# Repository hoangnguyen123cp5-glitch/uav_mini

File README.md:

# UAV Mini — nền tảng drone học thuật chi phí thấp

**Mục tiêu:** phát triển kit học điều khiển từ Flix, có log, bài thực hành và hướng mở rộng ToF/optical flow. Crazyflie là mốc tham chiếu tính năng; chưa tuyên bố tương đương hoặc tương thích.

**Trạng thái 03/11/2026:** chưa mua phần cứng. Đã có **project KiCad DRAFT-0** với schematic và PCB bố trí thử (33 linh kiện, chưa đi dây), cùng firmware **chạy bàn, khóa đầu ra motor**, công cụ phân tích log và ngân sách mục tiêu. Chưa có thử nghiệm bay hoặc PCB hoàn chỉnh để gia công.

| Bắt đầu ở đây | Nội dung |
|---|---|
| [Mở project KiCad trên máy](hardware/kicad/UAV_Mini_RevA_Draft/README.md) | File schematic/PCB, preview, kết quả kiểm tra và hướng dẫn Windows |
| [Lộ trình kit học thuật](docs/ACADEMIC_PRODUCT_ROADMAP.md) | Core Lab → Research → nhiều drone, ngân sách và ticket |
| [Firmware chạy bàn](firmware/README.md) | Cách tải đúng upstream, build, cấu hình và giới hạn |
| [Kết quả kiểm tra](docs/VALIDATION.md) | Kiểm tra phần mềm đã chạy và phần chưa xác minh |
| [Nguồn và PCB Rev A](docs/REV_A_POWER_AND_PCB.md) | Nguồn, USB, linh kiện và kế hoạch KiCad |
| [Nguồn gốc và thương mại hóa](docs/COMMERCIALIZATION_NOTES.md) | Tình trạng giấy phép, phân phối và thương hiệu |

Chạy ngay trên máy tính tại thư mục repo (cần Python 3):

```bash
python3 tools/budget.py
python3 tools/analyze_log.py examples/synthetic_log.csv
```

Ví dụ CSV là dữ liệu tổng hợp, không phải kết quả bay. Phần dưới giữ lại bài học KiCad và cấu hình tham khảo trước khi chốt phần cứng.

## Học vẽ mạch điều khiển bằng KiCad

**ESP32-S3 SuperMini + 4 motor chổi than + IMU + ToF + optical flow**  
Cập nhật: 03/11/2026 • Project hiện tại: `Flix_power`

UAV Mini là dự án học thiết kế mạch cho drone nhỏ, tham khảo dự án mã nguồn mở [Flix](https://github.com/okalachev/flix). Mục tiêu là làm một PCB mang bốn kênh điều khiển động cơ và các cổng cảm biến, với bo ESP32-S3 SuperMini cắm lên trên.

**Tài liệu dành cho người mới chưa biết bắt đầu vẽ schematic từ đâu.** Bạn sẽ lần lượt vẽ đầu pin, một kênh motor, nhân thành bốn kênh, nối bo S3 và các cổng cảm biến, rồi kiểm tra kết nối bằng ERC.

Schematic là sơ đồ các linh kiện nối điện với nhau. PCB là bản bố trí linh kiện và đường đồng để gia công. Tài liệu này hướng dẫn phần schematic; chưa phải hướng dẫn hoàn chỉnh từ đầu đến một drone bay được.

> Dự án đang phát triển. Các giá trị có chữ TBD và phần nguồn S3 chưa được chốt. Bạn có thể dùng tài liệu để học vẽ, nhưng chưa dùng bản hiện tại để đặt PCB hoặc lắp cấp điện. [Project KiCad DRAFT-0](hardware/kicad/UAV_Mini_RevA_Draft/README.md) đã được kiểm tra đọc/xuất và đối chiếu net, còn 67 mục chưa nối dây, chưa ERC hoặc kiểm chứng phần cứng. Bài thực hành bên dưới giữ lại quy trình cũ; bản CAD mới dùng MOSFET **G1/S2/D3**, khác thứ tự GDS trong bài cũ, và thêm cầu hàn ADC mặc định mở.

Các ảnh chụp KiCad ở bài thực hành A–E là ảnh thật ghi lại từng bước vẽ của dự án. Chú thích ngay dưới ảnh chỉ rõ phần nào còn là bước trung gian hoặc thuộc phương án cũ. Bốn hình sơ đồ chức năng ở các mục tham khảo được vẽ riêng để giải thích kết nối.

## Bắt đầu từ đâu?

1. Cài KiCad, tạo **New Project** tên `Flix_power` trong một thư mục riêng.
2. Mở file `.kicad_sch` bằng Schematic Editor.
3. Đọc phần “Các khái niệm cần biết” bên dưới.
4. Làm lần lượt bài thực hành A–F; dùng bảng chân và hình ở các mục sau để đối chiếu.
5. Lưu file sau mỗi khối. Chạy ERC để tìm lỗi kết nối trước khi chuyển sang bố trí PCB.

### Các khái niệm cần biết

| Tên | Hiểu đơn giản |
|---|---|
| Symbol | Ký hiệu linh kiện trên schematic |
| Reference | Mã nhận diện riêng: J là đầu nối, R là điện trở, C là tụ, Q là transistor, D là diode |
| Value | Giá trị hoặc mã linh kiện, ví dụ 10k, 100nF |
| Wire | Dây thể hiện kết nối điện |
| Net label | Tên mạng điện; các dây có cùng local label trên cùng sheet nối điện với nhau dù không kéo dây dài |
| GND | Điểm tham chiếu chung của mạch |
| Footprint | Hình chân hàn và kích thước linh kiện trên PCB; chọn sau khi chốt linh kiện thật |
| ERC | Công cụ tìm một số lỗi kết nối trên schematic |
| TBD | Chưa chọn xong; đây không phải mã linh kiện để mua |

**Label phải có điểm neo chạm dây.** Chữ đặt gần dây chưa chắc đã nối điện. Số chân của connector cũng không phải số GPIO trên ESP32.

## Thao tác KiCad từng lệnh — đọc trước khi vẽ

Hướng dẫn dùng Schematic Editor trên Windows, với phím tắt mặc định. Khi bấm phím, đưa con trỏ vào vùng vẽ; nếu đang nhập chữ trong hộp thoại, phím sẽ nhập chữ thay vì chạy lệnh. Nếu đã đổi phím tắt, kiểm tra trong **Preferences → Preferences → Hotkeys**.

### 1. Tạo project và mở trang vẽ

1. Mở KiCad Project Manager.
2. Chọn **File → New Project**, chọn thư mục và nhập tên Flix_power.
3. Giữ tùy chọn tạo thư mục riêng cho project nếu hộp thoại có tùy chọn này, rồi lưu.
4. Trong danh sách file của project, mở **Flix_power.kicad_sch**. Đây là trang vẽ sơ đồ nguyên lý.
5. Nếu lần đầu KiCad hỏi thiết lập thư viện symbol, chọn thư viện mặc định được cài cùng KiCad.
6. Dùng lưới **50 mil** để đặt chân và dây. Cuộn bánh xe chuột để phóng to khu vực đang vẽ.

### 2. A — thêm linh kiện

Ví dụ thêm đầu pin J1:

1. Đưa chuột tới khoảng trống, nhấn **A**.
2. Trong cửa sổ Choose Symbol, gõ **Conn_01x02_Pin** vào ô tìm kiếm.
3. Chọn đúng kết quả, nhìn hình xem có hai chân đánh số 1 và 2, rồi bấm **OK**.
4. Symbol đi theo con trỏ. Di chuyển tới nơi muốn đặt, bấm chuột trái một lần.
5. Nhấn **Esc** để thoát chế độ đặt; nếu còn công cụ hoạt động, nhấn Esc thêm lần nữa.

Dùng cùng thao tác này cho từng linh kiện:

| Cần vẽ | Từ khóa tìm bằng A | Reference theo bài | Value nhập bằng E |
|---|---|---|---|
| Đầu pin | Conn_01x02_Pin | J1 | BATTERY_1S |
| Đầu motor | Conn_01x02_Pin | J2–J5 | Motor_0 đến Motor_3 |
| Tụ phân cực | Device:C_Polarized | C1 | BULK_TBD |
| Tụ không phân cực | Device:C | C2, C3 | 100nF |
| Điện trở | Device:R | R1–R10 | Theo bảng từng khối |
| MOSFET N | Q_NMOS_GDS | Q1–Q4 | NMOS_TBD |
| Diode Schottky | Device:D_Schottky | D1–D4 | SCHOTTKY_TBD |
| Socket S3 | Conn_01x09_Socket | J7, J8 | S3_LEFT, S3_RIGHT |
| Đầu ToF | Conn_01x04_Pin | J6 | TOF_I2C |
| Đầu IMU/flow | Conn_01x06_Pin | J9, J10 | IMU_SPI, FLOW_SPI |

Nếu không tìm thấy, bỏ phần tên thư viện trước dấu hai chấm và tìm lại. Không chọn đại linh kiện có chân khác. Pin/Socket trong tên symbol biểu diễn loại đầu nối; footprint thật và kích thước hàng chân vẫn cần chọn riêng.

### 3. E — sửa tên và giá trị

1. Nhấn Esc để thoát công cụ trước đó.
2. Rê chuột lên **thân symbol** J1, nhấn **E**. Nếu xuất hiện danh sách nhiều đối tượng, chọn symbol cần sửa.
3. Trong Symbol Properties, tìm hàng **Reference**, nhập J1.
4. Tìm hàng **Value**, nhập BATTERY_1S; bấm **OK**.
5. Kiểm tra trên trang vẽ có cả J1 và BATTERY_1S.

Với điện trở, nhập Value là 100R hoặc 10k theo bài. Reference phải duy nhất: R1 và R2 là hai linh kiện khác nhau. Chưa chốt linh kiện thật thì để trống Footprint; không chọn footprint tùy ý chỉ để đi tiếp.

### 4. R — xoay; M — di chuyển

- **Xoay:** rê chuột lên thân điện trở → nhấn **R** một lần để xoay 90°; nhấn thêm nếu cần. Khi symbol đang đi theo chuột lúc đặt, cũng dùng R rồi bấm trái để đặt.
- **Di chuyển:** rê chuột lên symbol → nhấn **M** → đưa đến vị trí mới → bấm trái.
- Sau khi di chuyển một linh kiện đã nối dây, kiểm tra lại các đầu dây. Có thể dùng **G** để kéo linh kiện cùng dây, nhưng vẫn cần xem lại kết nối.
- Nhấn **Esc** để hủy thao tác chưa đặt. Nhấn **Ctrl+Z** để hoàn tác thay đổi vừa thực hiện.

### 5. W — nối dây điện

Ví dụ nối chân 1 của J1 đến cực dương C1:

1. Đặt C1 ở bên phải J1, cực + hướng lên trên.
2. Rê chuột đúng **đầu ngoài chân 1** của J1, không đặt lên số 1 hay chữ J1.
3. Nhấn **W**; di chuyển chuột để kéo dây.
4. Bấm trái tại vị trí muốn tạo góc rẽ, rồi tiếp tục tới đầu chân + của C1.
5. Bấm trái đúng đầu chân C1 để hoàn thành kết nối. Nhấn Esc để thoát công cụ.
6. Nếu muốn kết thúc một đoạn dây ở khoảng trống để đặt label, **nhấp đúp** tại điểm cuối rồi Esc.

Dây là đối tượng Wire, không dùng đường đồ họa để thay dây điện. Đầu dây phải bắt đúng chân trên lưới.

**Tạo nhánh:** rê chuột lên dây có sẵn → W → kéo tới chân linh kiện khác → bấm trái. Tại điểm nhánh nối điện sẽ có junction; không coi hai đường nhìn như chạm nhau là bằng chứng đủ nếu chưa kiểm tra điểm nối.

### 6. L — đặt tên mạng điện

Ví dụ đặt nhãn V_bat lên dây từ J1.1:

1. Nhấn Esc để thoát lệnh vẽ dây.
2. Rê chuột gần đoạn dây, nhấn **L**.
3. Nhập đúng **V_bat** trong hộp thoại Label Properties → OK.
4. Nhãn đi theo chuột: đưa **điểm neo của nhãn** chạm đoạn dây, bấm trái để đặt.
5. Nhấn Esc. Muốn đổi tên, rê lên nhãn và nhấn E.

Làm tương tự với M0_NEG và PWM_M0. Không dùng **T (text)** để tạo tên mạng: chữ ghi chú không tạo kết nối điện. Các local label cùng tên trên cùng sheet thuộc cùng mạng; không tự suy ra kết nối qua các sheet khác nhau.

### 7. P — đặt GND

1. Rê chuột vào khoảng trống dưới linh kiện, nhấn **P**.
2. Tìm **GND**, chọn symbol power:GND → OK.
3. Đặt symbol dưới chân cần nối, bấm trái rồi Esc.
4. Rê đúng đầu chân linh kiện → W → kéo tới điểm nối phía trên symbol GND → bấm trái.
5. Tất cả symbol GND dùng chung mạng điện; không cần vẽ dây dài nối mọi ký hiệu GND với nhau.

Không đổi tên nguồn 5V thành 3V3 để hết cảnh báo. Label và ký hiệu nguồn không tạo ra điện áp vật lý.

### 8. Ctrl+D — nhân bản một khối

1. Nhấn Esc để không còn công cụ đang chạy.
2. Kéo một khung chọn **từ trái sang phải**, bao trọn linh kiện, dây và nhãn của một kênh motor.
3. Kiểm tra các đối tượng cần sao chép đều được chọn; không lấy cả khối pin nếu chỉ muốn nhân motor.
4. Nhấn **Ctrl+D**, đưa bản sao sang bên phải, bấm trái rồi Esc.
5. Sửa Reference của bản sao theo bảng mục 4 nếu cần; tránh trùng với bản gốc.
6. Rê lên từng nhãn → E: PWM_M0 thành PWM_M1, và **cả ba** M0_NEG thành M1_NEG.
7. Lặp lại cho kênh 2 và 3; giữ nguyên V_bat và GND.

Nhân bản không tự hiểu đâu là tín hiệu dùng chung, đâu là tín hiệu riêng. Nếu quên đổi M0_NEG, hai kênh sẽ bị nối chung qua tên mạng.

### 9. Delete, Ctrl+Z, Esc — sửa thao tác nhầm

- Rê lên đúng đối tượng cần bỏ → **Delete**. Nếu chọn nhầm, **Ctrl+Z** ngay.
- **Esc** hủy công cụ/selection hiện tại, không hoàn tác những gì đã đặt xong.
- Khi khó chọn dây vì gần chữ hoặc chân, phóng to và chọn đúng đối tượng trong danh sách KiCad hiện ra.
- Nếu đầu dây chưa bắt đúng chân, xóa đoạn sai rồi vẽ lại bằng W từ đầu chân. Không kéo chữ nhãn tới gần để che lỗi.

### 10. Lưu và chạy ERC

1. Nhấn **Ctrl+S**.
2. Chọn **Inspect → Electrical Rules Checker**.
3. Bấm **Run ERC**; hiển thị cả Errors và Warnings.
4. Nhấp đúp một dòng cảnh báo để KiCad đưa tới vị trí liên quan.
5. Sửa lỗi trên trang vẽ, lưu, chạy ERC lại. Đối chiếu xem đúng cảnh báo đó đã biến mất chưa.
6. Nếu Reference còn dạng R?/J? hoặc bị trùng, dùng **Tools → Annotate Schematic**; đọc lựa chọn trước khi áp dụng, giữ các Reference đã gán đúng. Khi số đổi, đối chiếu lại bảng hướng dẫn theo chức năng.

**Chỉ với chân thực sự không dùng:** bỏ dây/label thừa, rê đúng đầu chân rồi nhấn **Q** để đặt dấu No Connect. Không đánh Q lên chân cấp nguồn đang thiếu mạch nguồn. PWR_FLAG chỉ khai báo nguồn cho ERC, không thay thế mạch nguồn.

Thao tác tham khảo: [KiCad Schematic Editor 10.0](https://docs.kicad.org/10.0/en/eeschema/eeschema.html).

### Bài thực hành A — vẽ đầu pin

- Nhấn **A**, tìm `Conn_01x02_Pin`, đặt đầu nối J1; nhấn **E** đổi Value thành `BATTERY_1S`.
- Nhấn **W** từ chân 1, kéo một đoạn dây; nhấn **L** đặt nhãn `V_bat`.
- Nối chân 2 với ký hiệu GND bằng **P → GND**.
- Thêm tụ phân cực C1 và tụ không phân cực C2 song song giữa V_bat và GND, theo mục 5. Đặt C1 là `BULK_TBD`, C2 là `100nF`.
- Kiểm tra cực dương C1 nối V_bat. Đây là đầu vào pin, chưa phải mạch sạc.

**Thứ tự nối C1/C2 bằng W:**

1. A → Device:C_Polarized → đặt C1 → E → Value BULK_TBD. Xoay R nếu cần để cực + ở trên.
2. A → Device:C → đặt C2 bên phải C1 → E → Value 100nF.
3. W từ J1.1 tới chân + C1; W từ nút này sang chân trên C2.
4. W nối chân dưới C1 với chân dưới C2; đặt GND tại mạng này bằng P rồi nối W.
5. P → GND → đặt dưới J1.2; W nối J1.2 tới GND.
6. L → V_bat → đặt điểm neo lên dây J1.1. Ctrl+S.

**Ảnh chụp thực tế sau khi vẽ khối đầu pin:**

Hai ký hiệu GND thuộc cùng mạng điện. Chấm xanh tại chỗ rẽ thể hiện điểm nối dây. C1 vẫn chờ chọn giá trị thực tế.

### Bài thực hành B — vẽ một kênh motor

- Thêm đầu nối 2 chân J2, đổi Value thành `Motor_0`.
- Nối chân 1 tới nhãn `V_bat`, chân 2 tới `M0_NEG`.
- Thêm symbol `Q_NMOS_GDS` làm Q1 và hai điện trở R1, R2.
- Nối theo hình mục 4: PWM_M0 → R1 → Gate; R2 từ Gate xuống GND; Source xuống GND; Drain tới M0_NEG.
- Thêm diode Schottky D1: cathode tới V_bat, anode tới M0_NEG.
- Đặt giá trị tạm theo mục 4. Đối chiếu cả tên chân G/D/S và số chân trước khi nối.

#### B1. Đặt đầu nối motor

Nhấn **A** để thêm đầu nối 2 chân, **E** sửa Value thành Motor_0. Dùng **W** vẽ dây và **L** đặt V_bat/M0_NEG. Đặt Reference là J2; chữ Motor_0 là Value, không thay cho Reference.

#### B2. Thêm MOSFET

Nhấn **A**, tìm Q_NMOS_GDS. Đặt Drain lên trên, Source xuống dưới như ảnh; rê chuột lên symbol và nhấn **R** nếu cần xoay. Nối Drain tới M0_NEG, Source tới GND. Chân Gate bên trái sẽ nối ở bước B3.

Ảnh này là bước trung gian: Gate còn hở. Vẽ dây GND gọn, tránh đoạn dây gấp ngược như trong ảnh. Không cần kéo dây dài từ motor tới Drain: hai nhãn M0_NEG cùng sheet tạo kết nối.

#### B3. Thêm điện trở điều khiển Gate

Nhấn **A**, tìm symbol điện trở R và đặt R1 nằm ngang; dùng **R** để xoay. Nhấn **E** đặt Value 100R. Thêm R2 đứng dọc, Value 10k, nối từ nút giữa R1 và Gate xuống GND. Đầu còn lại của R1 đặt nhãn PWM_M0.

Đối chiếu chấm nối xanh ở nhánh R2: nhánh này phải nối vào phía Gate của R1.

#### B4. Thêm diode hồi dòng

Nhấn **A**, tìm symbol D_Schottky. Xoay để cathode (đầu có vạch gấp của ký hiệu Schottky) ở phía V_bat; anode nối M0_NEG. Đặt Reference D1 và Value SCHOTTKY_TBD trong giai đoạn chưa chọn mã thật.

Ảnh cũ ghi CHOTTKY_TKD; dùng tên SCHOTTKY_TBD trong bài vẽ. Đây là giá trị tạm, không phải mã linh kiện.

#### B5. Đối chiếu cả kênh

Theo dõi ba điểm mang nhãn M0_NEG: đầu motor, diode và Drain. Cả ba phải viết cùng một tên. Gate phải có cả điện trở nối tiếp và điện trở kéo xuống.

### Bài thực hành C — tạo đủ bốn kênh

Nhân bản khối motor ba lần. Dùng bảng mục 4 để sửa Reference và tên nhãn từng kênh. Cả bốn kênh dùng chung V_bat và GND; mỗi kênh phải có PWM và Mn_NEG riêng. Khi KiCad tự đánh số khác bảng, có thể sửa Reference để thống nhất; tuyệt đối không để hai linh kiện trùng Reference.

**Kết quả bố trí bốn kênh trong KiCad:**

Chọn cả khối một kênh rồi nhân bản bằng **Ctrl+D**. Sửa nhãn kênh 1, 2, 3 ngay sau mỗi lần nhân; bảng mục 4 liệt kê tên cần dùng. Giữ V_bat/GND chung cho tất cả kênh.

### Bài thực hành D — socket S3 và đo pin

- Thêm hai socket 9 chân làm J7/J8. Đây là chỗ cắm bo S3 lên PCB.
- Kéo dây ngắn và đặt nhãn từng chân theo bảng mục 3.
- Vẽ R9, R10 và C3 theo mục 5; nối điểm giữa tới `VBAT_SENSE`.
- Phân biệt rõ J8.1 là `S3_5V`, J8.3 là `S3_3V3`. Phần tạo nguồn cấp S3 vẫn chờ hoàn thiện ở mục 7.

**Thao tác vẽ hai socket:**

1. A → Conn_01x09_Socket → đặt J7 → E sửa Value S3_LEFT.
2. A → Conn_01x09_Socket → đặt J8 → E sửa Value S3_RIGHT.
3. Nếu chiều chân không giống ảnh, vẫn nhận diện theo số chân; dùng R để xoay nếu cần. Không lấy vị trí trên/dưới thay cho số chân.
4. Tại mỗi đầu chân: W → kéo đoạn dây ngắn → nhấp đúp kết thúc → Esc.
5. L → nhập tên nhãn trong bảng mục 3 → đặt điểm neo lên đoạn dây đó → Esc.
6. Riêng chân J8.2, đặt GND bằng P và nối W.
7. Kiểm tra lần lượt chân 1 đến 9 của cả hai socket trước khi lưu.

**Ảnh quá trình vẽ mạch đo pin — chỉ làm theo khối bên phải:**

Nhấn **A** đặt hai điện trở, dùng **R** xoay đứng, **E** đặt mỗi con 10k. Nối R9 từ V_bat tới nút giữa, R10 từ nút giữa xuống GND. Thêm C3 100nF từ nút giữa xuống GND, rồi đặt nhãn VBAT_SENSE tại nút giữa.

**Đầu J6 TO_MCU bên trái thuộc phương án cũ, không vẽ lại.** Thiết kế hiện tại dùng J7/J8 cắm trực tiếp S3; J6 được dùng làm cổng ToF. Dùng bảng chân mục 3 để vẽ hai socket S3.

### Bài thực hành E — cổng cảm biến

Thêm đầu nối 4 chân J6 cho ToF, đầu nối 6 chân J9 cho IMU và J10 cho optical flow. Gắn nhãn theo bảng mục 6. Các đầu nối này chỉ đại diện cổng trên PCB; khi dùng module thật phải đối chiếu thứ tự chân module trước khi làm dây.

**Thao tác cho từng cổng:**

1. A → Conn_01x04_Pin → đặt → E sửa Reference J6 và Value TOF_I2C.
2. W vẽ đoạn dây ngắn từ mỗi chân; kết thúc đoạn bằng nhấp đúp rồi Esc.
3. L đặt nhãn: chân 1 S3_3V3, chân 3 I2C_SDA, chân 4 I2C_SCL; chân 2 nối GND bằng P/W.
4. A → Conn_01x06_Pin → đặt → E sửa Reference J9, Value IMU_SPI.
5. Vẽ dây và nhãn cho sáu chân J9 theo bảng mục 6, đặc biệt chân 6 IMU_CS.
6. Chọn cả khối J9 → Ctrl+D → đặt bản sao → E sửa Reference J10, Value FLOW_SPI.
7. Rê nhãn chân 6 trên bản sao → E → đổi IMU_CS thành FLOW_CS. Các chân 1–5 giữ theo bảng.
8. Ctrl+S và chạy ERC.

Ảnh tổng thể dưới đây cho thấy các đầu nối nằm ở phía trên của sơ đồ:

Đây là ảnh trong quá trình vẽ, **còn lỗi nhãn J8.1**: khi thực hành phải đặt J8.1 = S3_5V, J8.3 = S3_3V3. Dùng bảng mục 3 và mục 6 để đối chiếu, không sao chép nguyên mọi nhãn trong ảnh. J9.6 phải là IMU_CS, J10.6 phải là FLOW_CS.

### Bài thực hành F — tự kiểm tra

Lưu sơ đồ, chạy ERC theo mục 8. Nhấp đúp từng cảnh báo để tìm vị trí, sửa kết nối rồi chạy lại. Đối chiếu bảng chân bằng mắt ngay cả khi ERC hết lỗi. Hoàn thành bài thực hành nghĩa là đã dựng được các khối schematic; phần nguồn, chọn linh kiện và layout vẫn cần các bước tiếp theo.

## 1. Kiến trúc dự án — một PCB

Bo S3 SuperMini cắm trực tiếp lên **J7/J8**. Bốn kênh công suất, đầu pin, đo pin, cổng IMU, ToF và optical flow nằm trên cùng PCB. Thiết kế dùng một PCB mang bo S3 và các đầu nối.

Mục tiêu phần mềm là dùng camera ngoài và máy tính để ước lượng vị trí, gửi dữ liệu hoặc lệnh qua Wi-Fi. S3 đọc cảm biến và điều khiển tư thế trên drone. ToF đo khoảng cách sàn; optical flow hỗ trợ ước lượng chuyển động ngang. Cần phát triển phần mềm kết hợp cảm biến và điều khiển vị trí, không chỉ cắm đủ phần cứng.

**Số đầu nối dùng thống nhất trong toàn tài liệu:**

| Reference | Chức năng | Symbol đang dùng / dự kiến |
|---|---|---|
| J1 | Pin LiPo 1S | Conn_01x02_Pin |
| J2–J5 | Motor 0–3 | Conn_01x02_Pin |
| J6 | TOF_I2C, 4 chân | Conn_01x04_Pin |
| J7 | S3_LEFT, 9 chân | Conn_01x09_Socket |
| J8 | S3_RIGHT, 9 chân | Conn_01x09_Socket |
| J9 | IMU_SPI, 6 chân | Conn_01x06_Pin |
| J10 | FLOW_SPI, 6 chân | Conn_01x06_Pin |

## 2. Phạm vi hiện tại

| Đã có trong hướng dẫn | Còn phải hoàn thiện |
|---|---|
| Cách vẽ đầu pin và bốn kênh motor | Chọn mã MOSFET, diode và tụ bulk |
| Bảng kết nối S3 và cổng cảm biến | Xác minh đúng phiên bản bo và module thực tế |
| Mạch chia áp đo pin | Nguồn S3, ngân sách dòng và xử lý nguồn USB |
| Quy trình kiểm tra ERC | File KiCad kiểm chứng, footprint, layout và DRC |

Các kết nối trong tài liệu là phương án thiết kế đang phát triển. Chưa có kết quả thử phần cứng hoặc thử bay của PCB này.

## 3. Socket S3 — bảng chân chuẩn của thiết kế

Nhìn mặt linh kiện bo S3, USB hướng lên. Chân socket 1–9 là số tự quy ước từ trên xuống, **không phải số GPIO**. Bảng lấy theo ảnh pinout người dùng cung cấp; cần kiểm tra với đúng bo mua thực tế trước khi làm footprint.

| Chân | J7 — chân S3 | Nhãn J7 | J8 — chân S3 | Nhãn J8 |
|---|---|---|---|---|
| 1 | TX | S3_TX | 5V | **S3_5V** |
| 2 | RX | S3_RX | GND | GND |
| 3 | GPIO1 | VBAT_SENSE | 3V3 | **S3_3V3** |
| 4 | GPIO2 | FLOW_CS | GPIO13 | SPI_MISO |
| 5 | GPIO3 | S3_GPIO3 | GPIO12 | SPI_SCK |
| 6 | GPIO4 | PWM_M0 | GPIO11 | SPI_MOSI |
| 7 | GPIO5 | PWM_M1 | GPIO10 | IMU_CS |
| 8 | GPIO6 | PWM_M2 | GPIO9 | I2C_SCL |
| 9 | GPIO7 | PWM_M3 | GPIO8 | I2C_SDA |

### Cách đặt dây và nhãn trong KiCad

1. Rê chuột lên nhãn, nhấn **E**, nhập đúng tên trong bảng.
2. Nếu chưa có dây: rê đúng đầu chân, nhấn **W**, kéo đoạn dây rồi Esc.
3. Nhấn **L** đặt nhãn; điểm neo phải chạm dây.
4. Với GND, dùng **P → GND**, nối đầu chân ký hiệu vào dây.

**S3_5V và S3_3V3 là hai mạng khác nhau. Không nối chung, không đổi tên để hết cảnh báo.** S3_TX/RX và GPIO3 đang dự phòng; chưa xác minh số GPIO của TX/RX. GPIO3 là chân strapping, tránh gán tải tùy ý. USB dùng GPIO19/20 trên chip.

## 4. Bốn kênh motor

Hình dùng khối Q1 để chỉ G/D/S rõ ràng; trong KiCad dùng symbol MOSFET. Symbol minh họa có **G=1, D=2, S=3**, tương ứng kiểu `Q_NMOS_GDS`. Khi chọn linh kiện thật phải đối chiếu lại datasheet, không mặc định mọi MOSFET đều có số chân này.

### Kết nối của từng kênh

- Đầu motor chân 1 → `V_bat`; chân 2 → `Mn_NEG`.
- Drain MOSFET → `Mn_NEG`; Source → GND.
- `PWM_Mn` → điện trở nối tiếp Gate → Gate.
- Điện trở kéo xuống nối **từ Gate phía sau điện trở nối tiếp** xuống GND.
- Diode hồi dòng: **K/cathode → V_bat**, **A/anode → Mn_NEG**. Không mắc diode xuống GND.

| Motor | Đầu nối | MOSFET | Diode | R Gate | R kéo xuống | PWM | Đầu âm motor |
|---|---|---|---|---|---|---|---|
| 0 | J2 | Q1 | D1 | R1 | R2 | PWM_M0 | M0_NEG |
| 1 | J3 | Q2 | D2 | R3 | R4 | PWM_M1 | M1_NEG |
| 2 | J4 | Q3 | D3 | R5 | R6 | PWM_M2 | M2_NEG |
| 3 | J5 | Q4 | D4 | R7 | R8 | PWM_M3 | M3_NEG |

Giá trị ban đầu: R Gate **100R**, R kéo xuống **10k**. Giá trị 100R chưa chốt; phải xét GPIO, điện tích cổng, tổn hao chuyển mạch và tần số PWM. Q1–Q4 đang `NMOS_TBD`; D1–D4 đang `SCHOTTKY_TBD`. Sửa lỗi chữ `CHOTTKY...` nếu còn, nhưng chưa coi đây là mã để mua.

Khi nhân kênh, đổi đủ ba nhãn Mn_NEG tại đầu motor, diode và Drain. Không được để cùng nhãn NEG giữa các motor.

## 5. Đầu pin và đo điện áp

### Đầu pin

- J1.1 → `V_bat`; J1.2 → GND.
- C1 phân cực: cực + → V_bat, cực còn lại → GND. Value `BULK_TBD` chờ chọn.
- C2 = 100nF, song song C1.

### Chia áp

```text
             V_bat
               │
            R9 10k
               │
               ├──────── VBAT_SENSE ── J7.3 / GPIO1
               │               │
           R10 10k          C3 100nF
               │               │
              GND             GND
```

Hai điện trở bằng nhau cho `VBAT_SENSE = V_bat / 2`: pin 4,2 V → 2,1 V ở ADC. Dự kiến dùng điện trở 1%, cấu hình attenuation ADC phù hợp và hiệu chuẩn phần mềm. Mạch này không sạc hoặc bảo vệ pin. Cần kiểm tra tình huống pin còn nối nhưng S3 mất nguồn để tránh cấp điện ngoài ý muốn qua chân ADC.

Nhãn chuẩn là **VBAT_SENSE**, không phải `VBAT_SENCE`. KiCad coi hai tên này là hai mạng khác nhau.

## 6. Cổng IMU, ToF và optical flow

**Đây là cổng nối dây do thiết kế quy ước. Không cắm module theo số chân bên dưới nếu chưa đối chiếu chân thực tế của module.** Dùng module có nguồn/logic tương thích 3,3 V hoặc bổ sung chuyển mức phù hợp. Không cấp chip cảm biến trần theo pinout module.

| Chân | J6 — TOF_I2C | J9 — IMU_SPI | J10 — FLOW_SPI |
|---|---|---|---|
| 1 | S3_3V3 | S3_3V3 | S3_3V3 |
| 2 | GND | GND | GND |
| 3 | I2C_SDA | SPI_SCK | SPI_SCK |
| 4 | I2C_SCL | SPI_MOSI | SPI_MOSI |
| 5 | — | SPI_MISO | SPI_MISO |
| 6 | — | **IMU_CS** | **FLOW_CS** |

### I²C — ToF

GPIO8/J8.9 = SDA; GPIO9/J8.8 = SCL. Kiểm tra điện trở kéo lên có sẵn trên module, điện áp được kéo lên và tải bus trước khi chọn điện trở bổ sung. Không tự cộng thêm 4,7k theo thói quen nếu module đã có pull-up. Xem yêu cầu XSHUT/INT theo module và cách sử dụng.

ToF gắn nhìn xuống sàn, không bị pin/khung che; dây ngắn và cố định chắc. Khoảng cách đo cần hiệu chỉnh theo tư thế để suy ra độ cao. Giới hạn đo tùy module, bề mặt và ánh sáng.

### SPI — IMU và optical flow

Chung GPIO12 SCK, GPIO11 MOSI, GPIO13 MISO. **IMU_CS = GPIO10**, **FLOW_CS = GPIO2**. Hai CS phải tách riêng. Kiểm tra mức deselect lúc khởi động và pull-up CS theo module thực tế.

Dự kiến optical flow PMW3901 dạng module SPI; IMU dạng module mà Flix hỗ trợ, ví dụ GY-91 sau khi xác nhận chip thực tế. Không đổi sang module chỉ có I²C mà giữ nguyên cổng SPI này.

Phương án hiện tại không dành chân INT riêng cho IMU/flow; cần xác nhận driver hỗ trợ polling. Phần mềm quản lý mode/tốc độ SPI theo thiết bị và lịch đọc để optical flow không làm trễ vòng IMU. Cần đo tải tổng trước khi dùng nguồn 3V3 của bo S3 cấp tất cả module.

## 7. Phần nguồn — đặc tả Rev A

Đã bổ sung [đặc tả nguồn, ngân sách dòng, ma trận thử và kế hoạch triển khai PCB](docs/REV_A_POWER_AND_PCB.md). Đây là tài liệu thiết kế, chưa phải schematic hoặc PCB đã kiểm chứng.

**Phương án thử ưu tiên:** LiPo 1S cấp trực tiếp bốn motor; nhánh logic dùng boost 5 V, qua khối chọn nguồn/chặn ngược, tới S3_5V; ổn áp trên SuperMini tạo 3,3 V. Việc dùng rail này cho cảm biến phụ thuộc khả năng dòng và nhiệt thực tế.

**Điểm chặn bắt buộc:** xác minh VBUS USB có nối cứng với S3_5V hay không. Mux trên PCB mẹ không giải quyết được đường nối đi vòng trên bo SuperMini. Cần cách ly đúng vị trí hoặc chọn nguồn bằng phần cứng đã kiểm chứng. USB chỉ cấp logic/debug, không cấp motor và không sạc pin qua boost.

| Kiến trúc | Đánh giá |
|---|---|
| 1S → boost 5 V → ổn áp SuperMini | Thuận tiện thử; phải kiểm tra tổn hao LDO và USB |
| 1S → buck-boost 3,3 V | Hướng tối ưu; phải xử lý ổn áp có sẵn và USB trước khi cấp vào 3V3 |
| 1S → LDO/buck 3,3 V | Mất điều áp khi pin thấp; không ưu tiên toàn dải xả |
| 1S → boost 3,3 V | Không bảo đảm hạ pin đầy xuống 3,3 V |
| 1S → trực tiếp 3V3 | Không được phép |

Espressif khuyến nghị nguồn 3,3 V có năng lực ít nhất 500 mA cho S3; đây không phải dòng tiêu thụ cố định. Cần cộng tải cảm biến, tải phụ, xung RF và dự phòng. Ví dụ giả định 600 mA liên tục qua LDO 5 V → 3,3 V gây khoảng 1,02 W tổn hao: chưa thể khẳng định ổn áp trên SuperMini chịu được.

TPS61023 (boost), TPS63070/TPS63031 (buck-boost), TPS2116 (mux) chỉ là ứng viên khảo sát, chưa duyệt BOM. Không nhầm giới hạn dòng công tắc với dòng đầu ra.

Trước khi chốt schematic cần mã/revision SuperMini, motor và cánh, pin, module cảm biến, module nguồn và kích thước PCB. Các mã MOSFET/Schottky/tụ bulk vẫn TBD. Không nối LiPo 4,2 V trực tiếp vào 3V3, không nối S3_5V với S3_3V3.

## 8. Khắc phục và chạy lại ERC

ERC giúp tìm các điểm nối còn thiếu hoặc cách khai báo chân chưa phù hợp. Những cảnh báo thường gặp khi làm bài này:

| Cảnh báo | Cách xử lý |
|---|---|
| Unconnected wire endpoint | Kiểm tra đầu dây và điểm neo nhãn; vẽ lại đoạn dây nếu chưa chạm |
| Local and global labels have same name | Với GND, thống nhất dùng symbol power:GND |
| Label connected to only one pin | Kiểm tra xem thiếu kết nối hay chân được chủ ý để dự phòng; nguồn S3 chưa hoàn thiện cũng cần kiểm tra |

### Quy trình

1. **Ctrl+S → Inspect → Electrical Rules Checker → Run ERC**.
2. Bật cả Errors và Warnings; xuất báo cáo mới.
3. Với đầu dây hở: phóng to, bắt đầu **W** đúng đầu chân; đặt điểm neo nhãn lên dây, không chỉ đặt chữ gần dây.
4. Với chân thực sự không dùng: chỉ đặt No Connect trực tiếp chân sau khi quyết định không dùng và gỡ dây/nhãn thừa. Không làm vậy với S3_5V đang chờ nguồn.
5. Chỉ thêm PWR_FLAG tại mạng thực sự được cấp nguồn khi ERC cần khai báo; cờ này không tạo ra nguồn điện.
6. Nếu dùng sheet con, kiểm tra kết nối giữa các sheet. Sheet con không tự tạo PCB thứ hai.
7. Bật lại kiểm tra footprint filter đang bị bỏ qua khi chốt footprint. Ghi lý do cho mọi cảnh báo cố ý giữ lại.

**ERC không phát hiện mọi lỗi:** chân connector passive có thể không báo thiếu nguồn; nhãn sai nhưng có kết nối vẫn có thể qua kiểm tra; chọn sai MOSFET hoặc điện áp module cũng không được đảm bảo bởi ERC.

## 9. Danh sách cần chốt để hoàn thành schematic

| Hạng mục | Cần xác định | Trạng thái |
|---|---|---|
| S3 SuperMini | Đúng bo/revision, schematic nguồn, kích thước hàng chân | Chờ |
| Q1–Q4 | Mã MOSFET, pinout, RDS(on) ở mức Gate phù hợp, Qg, nhiệt | Chờ |
| D1–D4 | Mã Schottky, dòng hồi tiếp, áp ngược, nhiệt, pinout | Chờ |
| C1 | Dung lượng, ESR, điện áp, kích thước | Chờ |
| R Gate | Xác nhận 100R theo linh kiện, GPIO và PWM | Tạm |
| Module nguồn | Mã, pinout, công suất và đường USB/cấp ngoài | Chờ |
| IMU | Mã module/chip, SPI, nguồn, hướng trục | Chờ |
| ToF | Mã module, nguồn/logic, pull-up, tầm đo | Chờ |
| Optical flow | Mã module SPI, nguồn, RESET/IRQ, chiều trục | Chờ |
| Header/motor/pin | Dòng, bước chân, cực tính và khóa cơ khí | Chờ |

### Điều kiện chuyển sang layout

- [ ] Tất cả mạng S3 đối chiếu đúng bảng chân và đúng bo thực tế.
- [ ] S3_5V/S3_3V3 tách biệt; đường cấp nguồn hoàn chỉnh.
- [ ] Đúng CS riêng, đúng SDA/SCL, VBAT_SENSE thống nhất.
- [ ] Mọi TBD đã thay bằng mã/giá trị xác định; symbol khớp pinout.
- [ ] Module và nguồn logic tương thích, đã tính dòng và tình huống khởi động/mất nguồn.
- [ ] ERC mới được xem đầy đủ; lỗi sửa xong, cảnh báo còn lại có giải thích.
- [ ] Footprint đã kiểm tra số pad, góc nhìn và kích thước thực tế.
- [ ] Bố trí sơ bộ có chỗ anten, lỗ bắt vít, dây motor và cửa nhìn cảm biến.

Sau đó mới layout, DRC, kiểm tra 3D, xuất Gerber/BOM. Cần tính khối lượng bo + socket + module + dây so với sức nâng motor 8520. Thử nguồn và từng motor khi tháo cánh trước khi thử điều khiển bay.

## 10. Phím nhanh

| Phím | Thao tác |
|---|---|
| A | Thêm symbol |
| E | Sửa thuộc tính dưới con trỏ |
| W | Vẽ dây từ đầu chân |
| L | Thêm nhãn mạng |
| P | Thêm nguồn/GND |
| R | Xoay 90 độ |
| Ctrl+D | Nhân bản; nhớ đổi Reference và nhãn riêng từng kênh |
| Esc | Thoát thao tác |
| Ctrl+S | Lưu |

Khi cần người khác kiểm tra, gửi file `.kicad_sch` cùng các sheet con, báo cáo ERC và mã module thực tế. Ảnh chụp giúp xem bố cục nhưng không xác nhận đầy đủ các kết nối.

## Nguồn và hình minh họa

### Ảnh schematic và bo S3 tham khảo

Ảnh dưới là **ảnh chụp schematic thật trong KiCad**, trước lần sửa nhãn nguồn cuối. Nó vẫn thể hiện lỗi J8.1 mang S3_3V3 và các dấu ERC cũ; **không sao chép lỗi này**. Bảng chân ở mục 3 là hướng dẫn hiện hành: J8.1 = S3_5V, J8.3 = S3_3V3. Ảnh này chỉ để nhận biết bố cục các khối, không phải sơ đồ hoàn thiện để sao chép.

Ảnh pinout S3 bên dưới do người dùng cung cấp; nguồn xuất bản gốc chưa xác định. Dùng để đối chiếu hình dạng và hàng chân, không thay thế schematic/datasheet đúng phiên bản bo. Chưa có ảnh PCB tự thiết kế đã gia công hoặc drone đã lắp hoàn chỉnh.

- [Flix — danh sách linh kiện và kết nối gốc](https://github.com/okalachev/flix#components)
- [Espressif — GPIO ESP32-S3](https://docs.espressif.com/projects/esp-idf/en/v5.0/esp32s3/api-reference/peripherals/gpio.html)
- [Bitcraze — Flow breakout, SPI và I²C](https://www.bitcraze.io/products/flow-breakout/)
- [Bitcraze — driver PMW3901](https://github.com/bitcraze/Bitcraze_PMW3901)

Bốn hình PNG trong thư mục `images/` được dựng riêng cho hướng dẫn này. Bảng socket S3 dựa trên ảnh pinout người dùng cung cấp; không phải tài liệu chứng nhận của nhà sản xuất bo.

## Video học thêm

- [Electrical Rules Check trên KiCad — einstem](https://www.youtube.com/watch?v=UgQMZtF_Wkw&t=27s): phần chạy ERC bắt đầu ở 0:27.
- [ERC và DRC trên KiCad 9 cho người mới](https://www.youtube.com/watch?v=OZhVRyuPJuA): xem phần ERC khi đang vẽ schematic, phần DRC khi làm PCB.
- [KiCad — Getting Started](https://docs.kicad.org/9.0/en/getting_started_in_kicad/getting_started_in_kicad.html): tài liệu chính thức về quy trình thiết kế.

## Đóng góp

Có thể mở Issue trong repository để hỏi về bước vẽ hoặc báo lỗi tài liệu. Khi báo lỗi, ghi phiên bản KiCad, bước đang làm và kèm ảnh hoặc file schematic liên quan. Không coi việc hoàn thành bài vẽ hoặc ERC hết lỗi là xác nhận drone đã sẵn sàng bay.

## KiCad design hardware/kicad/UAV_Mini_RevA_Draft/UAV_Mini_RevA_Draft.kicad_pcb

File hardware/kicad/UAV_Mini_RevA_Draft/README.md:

# UAV Mini Rev A — project KiCad DRAFT-0

Ngày 03/11/2026. **Đã có file schematic và PCB chỉnh sửa được. Đây là bản thiết kế điện và bố trí thử, chưa đi dây, chưa dùng để gia công hoặc cấp điện.**

## Mở trên máy Windows

1. Tải [ZIP của repository](https://github.com/hoangnguyen123cp5-glitch/uav_mini/archive/refs/heads/main.zip), chọn **Extract All**. Không mở file trực tiếp trong ZIP.
2. Trong KiCad 7 trở lên, chọn **File → Open Existing Project** rồi mở `hardware/kicad/UAV_Mini_RevA_Draft/UAV_Mini_RevA_Draft.kicad_pro`.
3. Mở `.kicad_sch` để xem sơ đồ; mở `.kicad_pcb` để xem bố trí và các đường nối chưa định tuyến (ratsnest).
4. Giữ nguyên `fp-lib-table` và thư mục `footprints` cùng project. Symbol được nhúng trong schematic; footprint dùng trong bản này có bản sao đi kèm.
5. Lưu bản sao trước khi sửa bằng phiên bản KiCad mới hơn. Phiên bản đã dùng để kiểm tra: **7.0.11**; chưa thử mở trên Windows hoặc các phiên bản khác.

Project được tạo trong môi trường làm việc của trợ lý rồi đưa vào repository; chưa có thao tác cài đặt hay sửa file trên máy của chủ dự án.

## File đã có

| File | Nội dung |
|---|---|
| `UAV_Mini_RevA_Draft.kicad_pro` | Project KiCad |
| `UAV_Mini_RevA_Draft.kicad_sch` | 33 symbol, bốn kênh motor, socket S3, cổng cảm biến, chia áp pin |
| `UAV_Mini_RevA_Draft.kicad_pcb` | 33 footprint, hai lớp đồng, biên 60 × 60 mm giả định; chưa có track/zone |
| `design.net.xml` | Netlist xuất bằng KiCad, dùng đối chiếu pad |
| `design_manifest.json` | Bảng chân và vị trí đề xuất; không phải BOM để đặt mua |
| `validation.json`, `drc-draft.txt` | Kết quả kiểm tra và lỗi chưa đi dây |
| `preview/` | SVG xuất trực tiếp từ KiCad |

[Xem toàn bộ schematic](preview/UAV_Mini_RevA_Draft.svg).

## Đã kiểm tra và chưa kiểm tra

- KiCad đọc được schematic, xuất SVG và netlist; `pcbnew` đọc lại được PCB đã lưu.
- Các chân có net trong schematic khớp bảng thiết kế và pad PCB. Đã đối chiếu riêng gate/source/drain, chiều diode và ba net nguồn tách biệt.
- DRC của bố trí hiện tại: **0 vi phạm khác, 67 mục kết nối chưa hoàn thành**, 0 lỗi footprint. **Không phải DRC đạt toàn bộ.** Quy tắc mặc định dùng cho kiểm tra này chưa thay thế thông số nhà máy và ngân sách dòng điện.
- Chưa chạy ERC; chưa đo phần cứng, thử nhiệt, tải xung, USB, motor hoặc bay. ERC sau này cũng không chứng minh nguồn đủ dòng hoặc pinout module đúng.
- Chưa có Gerber, BOM mua hàng, pick-and-place, lỗ bắt vít, keepout anten được xác nhận hoặc phê duyệt sản xuất.

## Các quyết định có chủ ý

**Nguồn còn hở:** `BOOST_5V` ở J11.3 chưa nối vào `S3_5V` ở J8.1. Vì chưa biết mạch VBUS của SuperMini, chưa có mạch chọn nguồn/cách ly USB hoàn chỉnh. Không hàn dây nối tắt khoảng hở này. `S3_5V` và `S3_3V3` là hai net riêng. J11 chỉ là quy ước giao tiếp module, không mô phỏng một module boost cụ thể.

**Chia áp ADC:** R9/R10 dự kiến 10 kΩ/10 kΩ, C3 dự kiến 100 nF. JP1 là cầu hàn **mặc định mở**, tách `VBAT_DIV` và `VBAT_SENSE`; chỉ xem xét đóng sau khi kiểm tra dòng tiêm ADC lúc S3 mất nguồn. Firmware bench vẫn tắt đo pin.

**Chân MOSFET:** bản CAD dùng `Q_NMOS_GSD`: **1=G, 2=S, 3=D**, footprint SOT-23 tạm. Bài học cũ ở README dùng `Q_NMOS_GDS` có thứ tự khác. Không lấy số chân trong bài cũ để lắp bản này. Cần đối chiếu datasheet mã MOSFET thực tế trước khi chốt.

**Diode:** pin 1=K nối V_bat, pin 2=A nối cực âm motor. SOD-123 là kích thước thử, không phải linh kiện đã đáp ứng dòng hoặc nhiệt.

**Cơ khí:** bo 60 × 60 mm và khoảng cách hai hàng socket 17,78 mm chỉ để khảo sát bố trí; chưa khớp SuperMini hoặc khung cụ thể. Độ dày 1,6 mm mặc định của KiCad chưa được chọn cho sản phẩm. Footprint header 2,54 mm, điện trở/tụ 0603 và tụ bulk radial 6,3 mm đều là giả định; không có chứng nhận dòng motor cho các đầu nối này.

**Cảm biến:** J6/J9/J10 dành cho module hoàn chỉnh có giao tiếp phù hợp 3,3 V, không dành cho IC cảm biến trần. Chưa chốt module nào, mạch ổn áp riêng, pull-up I²C, tụ lọc hay định hướng IMU. Chưa kiểm tra khả năng cấp dòng của S3_3V3. ADC và linh kiện dưới module S3 cần kiểm tra khoảng hở chiều cao.

## Cần chốt để tiếp tục định tuyến và làm PCB thử

| Hạng mục | Dữ liệu cần có | Ảnh hưởng thiết kế |
|---|---|---|
| SuperMini | Link nhà sản xuất, revision, sơ đồ nguồn, ảnh hai mặt, kích thước và khoảng cách chân | Socket, USB, nguồn logic, vùng anten |
| Motor/cánh/khung | Mã motor brushed, điện áp, dòng không tải/có cánh/khởi động/kẹt trục, đường cong lực nâng; cánh CW/CCW; bản vẽ khung | MOSFET, diode, bề rộng đồng, đầu nối, khối lượng và lỗ bắt |
| Pin | Mã pin 1S, điện áp sạc, dung lượng, dòng xả, đầu nối/cực tính, điện trở trong | Phân phối nguồn, sụt áp, bảo vệ và ngưỡng dừng |
| Q1–Q4 | Mã đặt hàng và datasheet; RDS(on) được đặc tả ở VGS phù hợp 3,3 V, SOA, điện tích gate, nhiệt | Pinout, package, tổn hao; không chọn chỉ theo VGS(th) |
| D1–D4 | Mã diode, VRRM, dòng trung bình/xung, VF, nhiệt | Package và khả năng chịu xung hồi tiếp |
| C1 | Điện dung, điện áp, ESR, ripple, kích thước/khối lượng | Sụt áp xung và bố trí vòng dòng motor |
| Boost/USB | Mã module/IC, dòng ở Vin thấp nhất, hiệu suất, startup, reverse-current behavior; đường VBUS của bo | Thiết kế nguồn còn thiếu; kiểm tra cả USB-only, battery-only và hai nguồn |
| IMU/ToF/flow | Mã module, sơ đồ, điện áp, dòng, pinout, mức logic và kích thước | Đầu nối và rail cảm biến |

Sau khi có dữ liệu: hoàn thiện mạch nguồn/bảo vệ, kiểm tra footprint 1:1 → ERC → định tuyến và plane GND theo dòng thực → DRC theo nhà máy → review → đặt ít PCB thử → kiểm tra nguồn giới hạn dòng, USB backfeed, ripple, nhiệt và motor trước thử bay.

## Tái tạo và kiểm tra bằng mã

Các file CAD đã lưu sẵn; người dùng Windows **không cần chạy Python** để mở/sửa bằng KiCad.

Người bảo trì dùng Python có module `pcbnew` và KiCad CLI:

```bash
python3 tools/verify_kicad_draft.py --cli kicad-cli
# Chỉ dùng sau khi đã lưu riêng mọi sửa tay; lệnh sau ghi đè CAD:
python3 tools/generate_kicad_draft.py --kicad-share /usr/share/kicad --overwrite
```

Generator không chạy các bước xuất preview/netlist hoặc kiểm tra thay cho `verify_kicad_draft.py`. Khi sửa CAD bằng tay, đó là nguồn làm việc mới; không chạy generator để ghi đè sửa tay. Sau khi đi dây, cập nhật trạng thái và bộ kiểm tra vốn đang yêu cầu đúng bản chưa đi dây.

Symbol nhúng và các footprint sao chép nguyên bản từ thư viện KiCad 7.0.11 (Ubuntu), KiCad Community; xem `KICAD_SYMBOLS_COPYRIGHT.txt` và `KICAD_FOOTPRINTS_COPYRIGHT.txt` (CC BY-SA 4.0 kèm ngoại lệ cho thiết kế điện tử). Chưa bao gồm model 3D; việc chọn footprint tạm không xác nhận linh kiện sẽ lắp vừa.

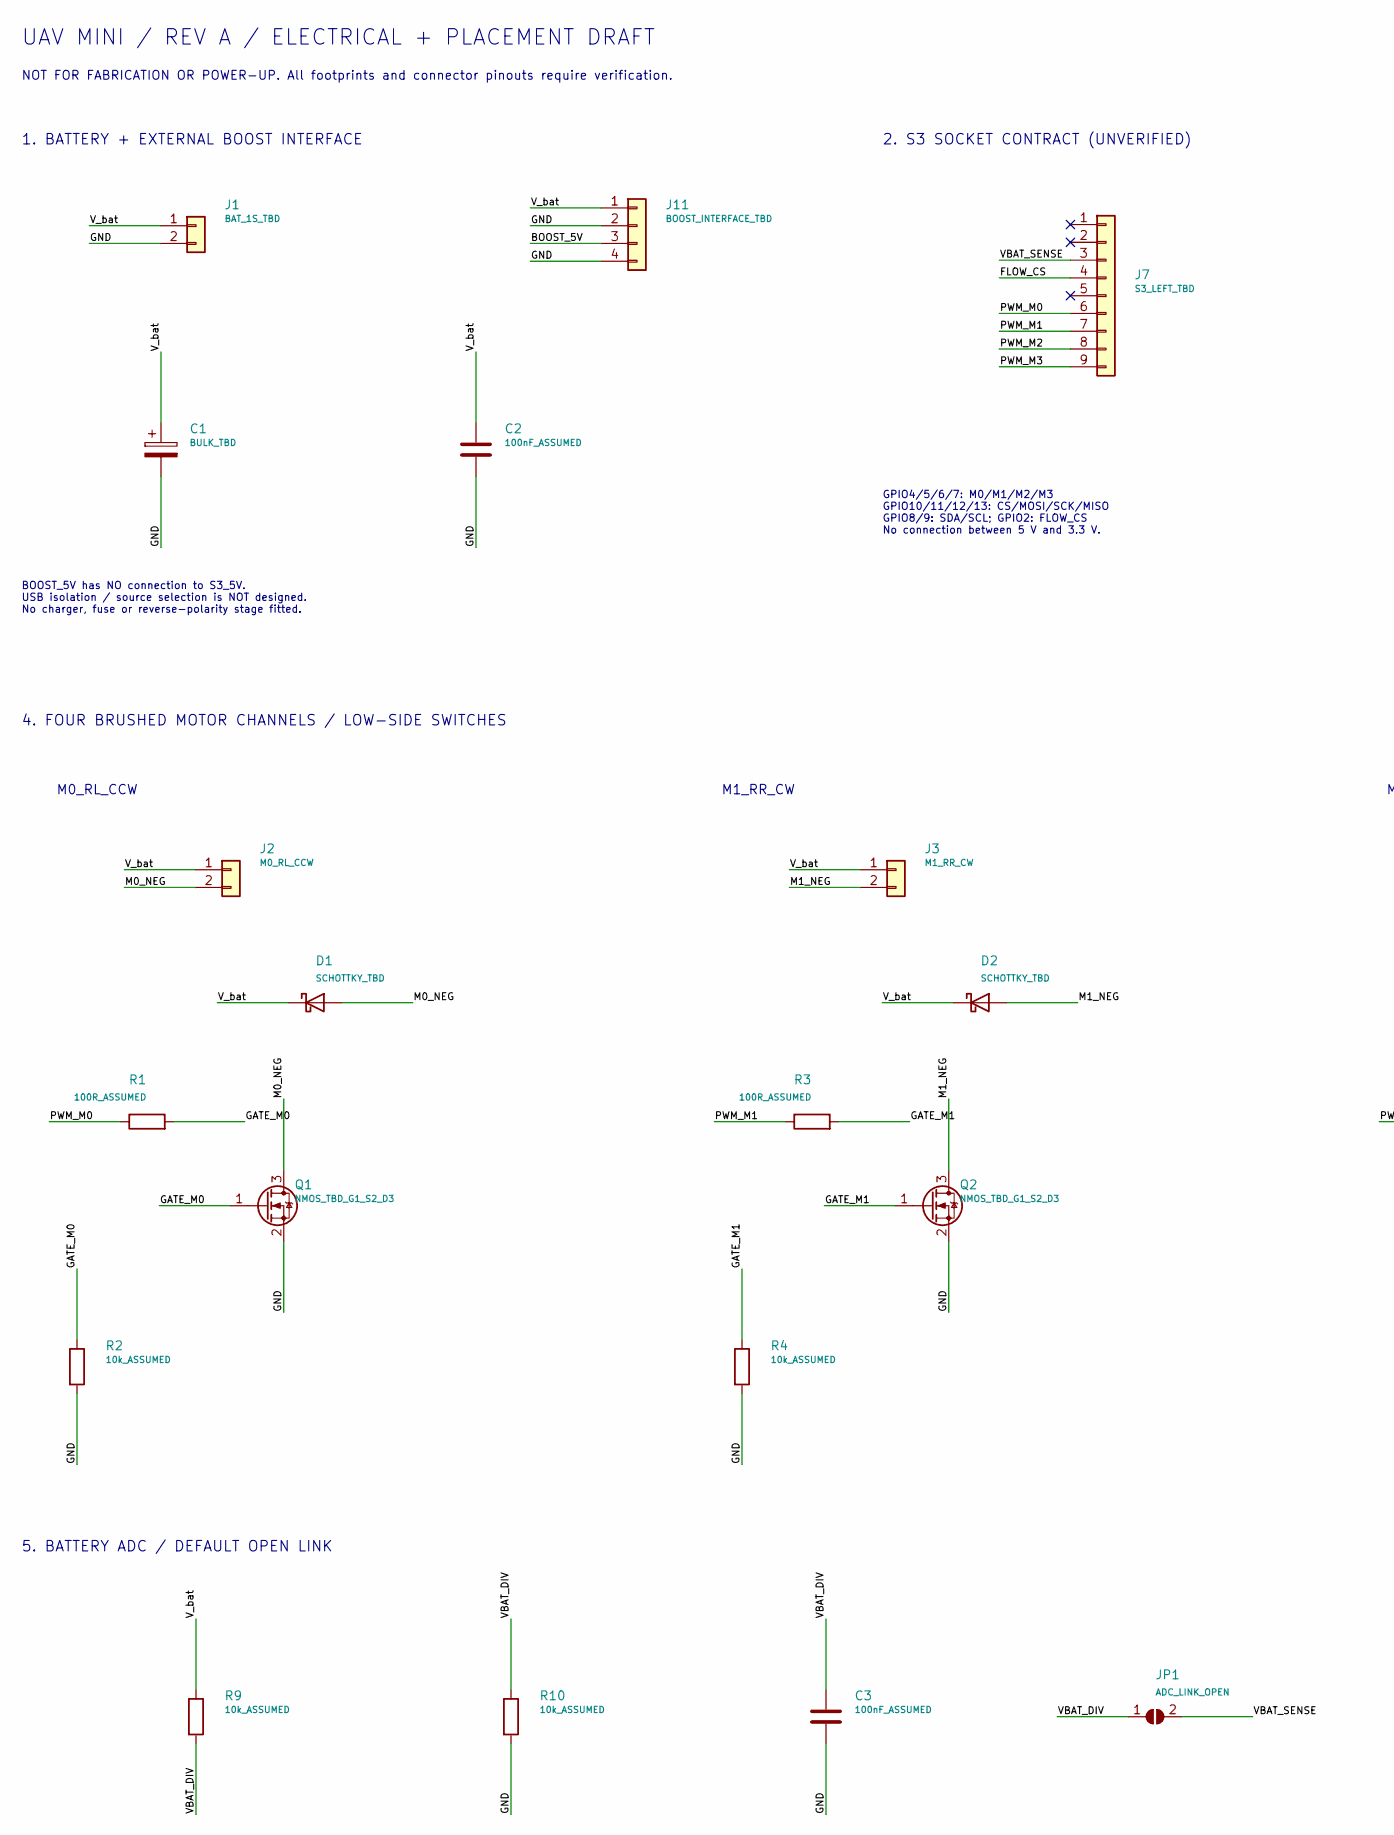
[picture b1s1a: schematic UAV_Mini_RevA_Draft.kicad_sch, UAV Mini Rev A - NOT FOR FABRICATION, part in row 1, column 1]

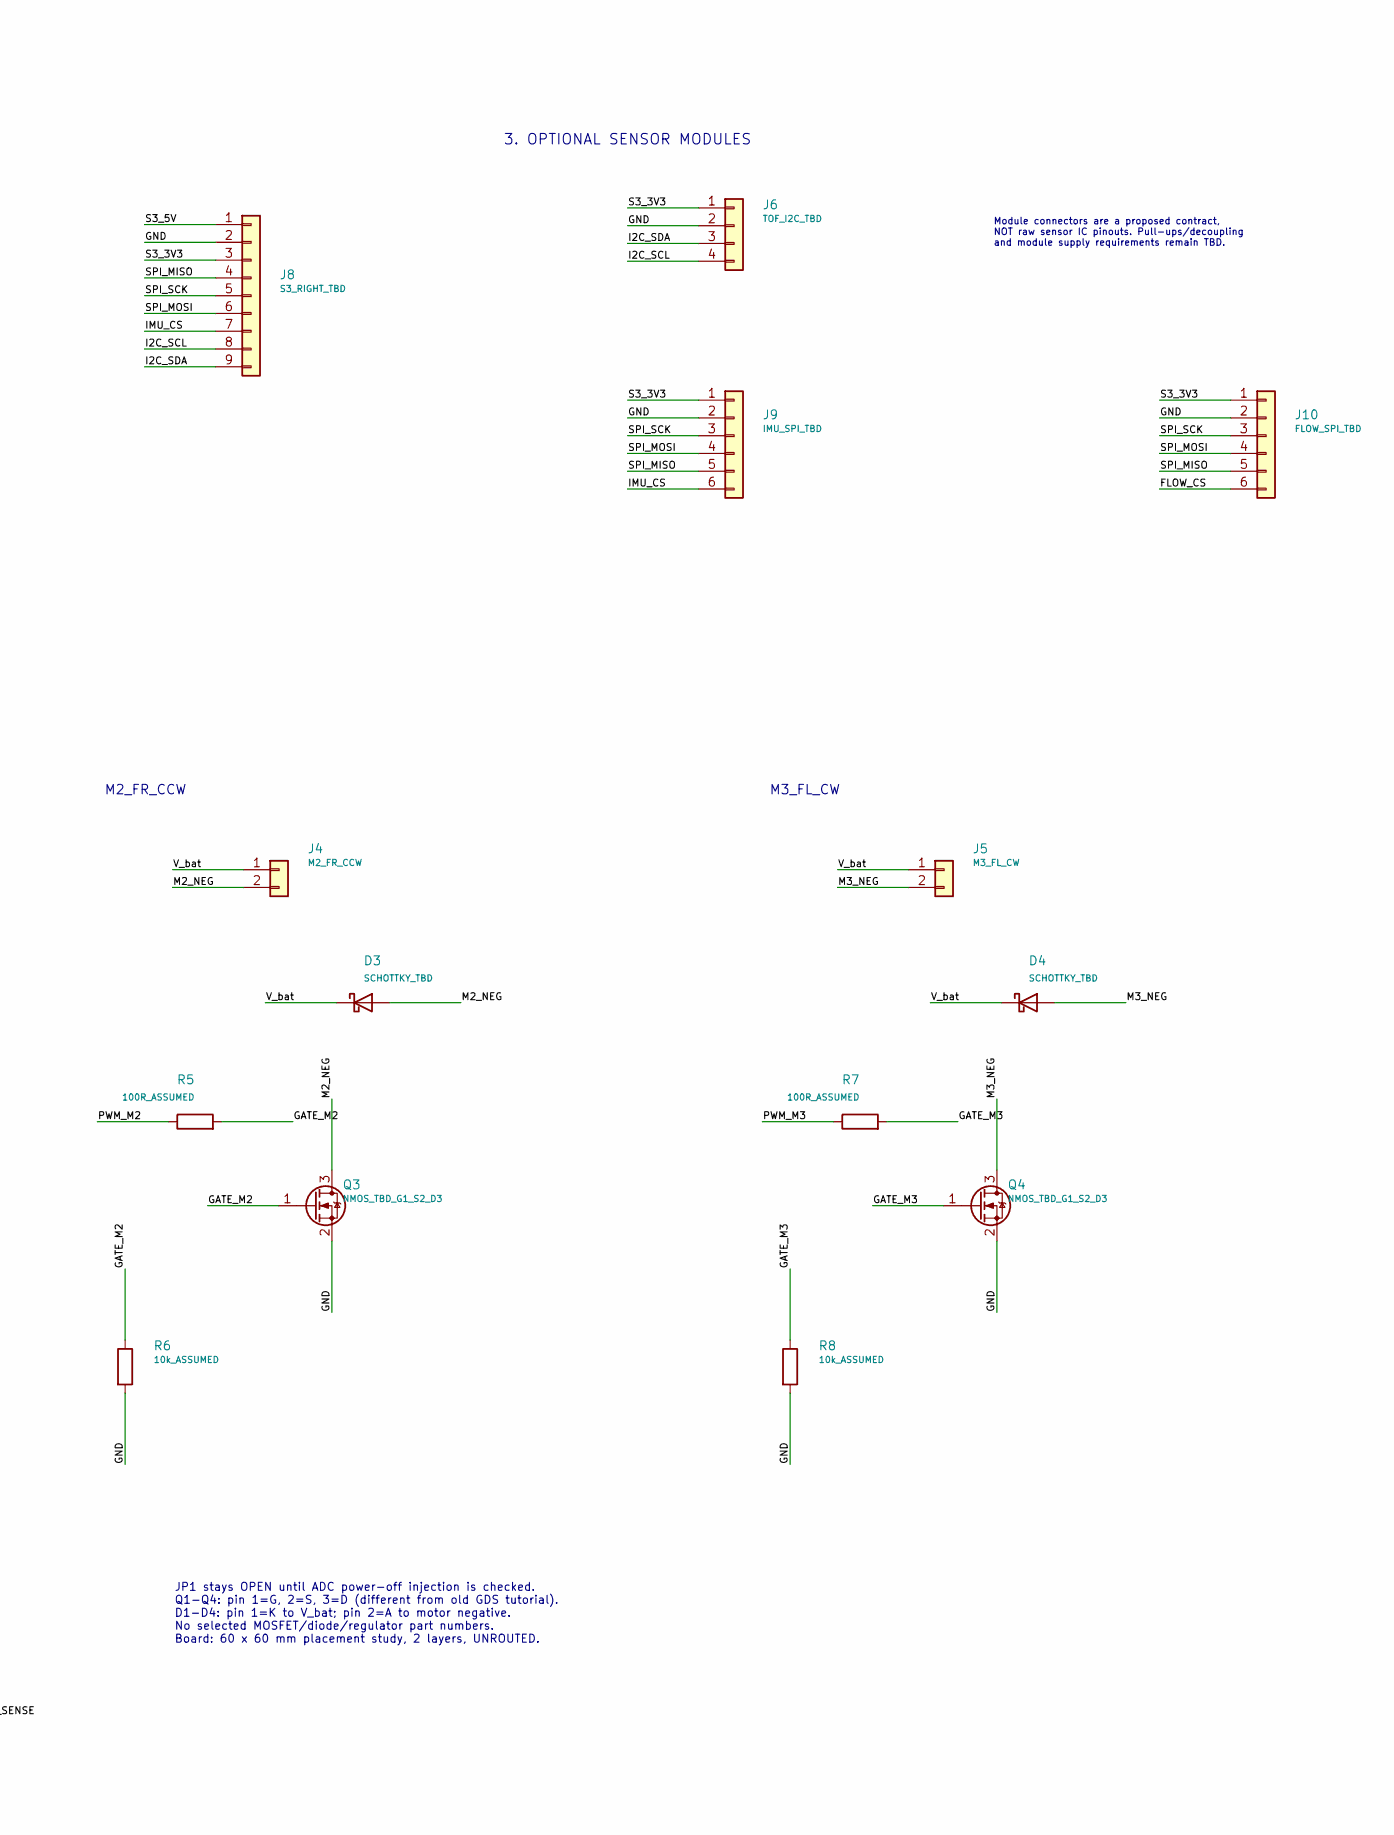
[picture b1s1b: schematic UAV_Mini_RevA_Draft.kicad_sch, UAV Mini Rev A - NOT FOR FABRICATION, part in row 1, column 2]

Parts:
C1: BULK_TBD; CP_Radial_D6.3mm_P2.50mm
C2, C3: 100nF_ASSUMED; C_0603_1608Metric
D1, D2, D3, D4: SCHOTTKY_TBD; D_SOD-123
J1: BAT_1S_TBD; PinHeader_1x02_P2.54mm_Vertical
J2: M0_RL_CCW; PinHeader_1x02_P2.54mm_Vertical
J3: M1_RR_CW; PinHeader_1x02_P2.54mm_Vertical
J4: M2_FR_CCW; PinHeader_1x02_P2.54mm_Vertical
J5: M3_FL_CW; PinHeader_1x02_P2.54mm_Vertical
J6: TOF_I2C_TBD; PinHeader_1x04_P2.54mm_Vertical
J7: S3_LEFT_TBD; PinSocket_1x09_P2.54mm_Vertical
J8: S3_RIGHT_TBD; PinSocket_1x09_P2.54mm_Vertical
J9: IMU_SPI_TBD; PinHeader_1x06_P2.54mm_Vertical
J10: FLOW_SPI_TBD; PinHeader_1x06_P2.54mm_Vertical
J11: BOOST_INTERFACE_TBD; PinHeader_1x04_P2.54mm_Vertical
JP1: ADC_LINK_OPEN; SolderJumper-2_P1.3mm_Open_Pad1.0x1.5mm
Q1, Q2, Q3, Q4: NMOS_TBD_G1_S2_D3; SOT-23
R1, R3, R5, R7: 100R_ASSUMED; R_0603_1608Metric
R2, R4, R6, R8, R9, R10: 10k_ASSUMED; R_0603_1608Metric

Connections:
BOOST_5V: J11.3
FLOW_CS: J7.4, J10.6
GATE_M0: Q1.1 (G), R1.2, R2.1
GATE_M1: Q2.1 (G), R3.2, R4.1
GATE_M2: Q3.1 (G), R5.2, R6.1
GATE_M3: Q4.1 (G), R7.2, R8.1
GND: C1.2, C2.2, C3.2, J1.2, J6.2, J8.2, J9.2, J10.2, J11.2, J11.4, Q1.2 (S), Q2.2 (S), Q3.2 (S), Q4.2 (S), R2.2, R4.2, R6.2, R8.2, R10.2
I2C_SCL: J6.4, J8.8
I2C_SDA: J6.3, J8.9
IMU_CS: J8.7, J9.6
M0_NEG: D1.2 (A), J2.2, Q1.3 (D)
M1_NEG: D2.2 (A), J3.2, Q2.3 (D)
M2_NEG: D3.2 (A), J4.2, Q3.3 (D)
M3_NEG: D4.2 (A), J5.2, Q4.3 (D)
PWM_M0: J7.6, R1.1
PWM_M1: J7.7, R3.1
PWM_M2: J7.8, R5.1
PWM_M3: J7.9, R7.1
S3_3V3: J6.1, J8.3, J9.1, J10.1
S3_5V: J8.1
SPI_MISO: J8.4, J9.5, J10.5
SPI_MOSI: J8.6, J9.4, J10.4
SPI_SCK: J8.5, J9.3, J10.3
VBAT_DIV: C3.1, JP1.1 (A), R9.2, R10.1
VBAT_SENSE: J7.3, JP1.2 (B)
V_bat: C1.1, C2.1, D1.1 (K), D2.1 (K), D3.1 (K), D4.1 (K), J1.1, J2.1, J3.1, J4.1, J5.1, J11.1, R9.1

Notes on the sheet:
UAV MINI / REV A / ELECTRICAL + PLACEMENT DRAFT
NOT FOR FABRICATION OR POWER-UP. All footprints and connector pinouts require verification.
1. BATTERY + EXTERNAL BOOST INTERFACE
BOOST_5V has NO connection to S3_5V. USB isolation / source selection is NOT designed. No charger, fuse or reverse-polarity stage fitted.
2. S3 SOCKET CONTRACT (UNVERIFIED)
GPIO4/5/6/7: M0/M1/M2/M3 GPIO10/11/12/13: CS/MOSI/SCK/MISO GPIO8/9: SDA/SCL; GPIO2: FLOW_CS No connection between 5 V and 3.3 V.
3. OPTIONAL SENSOR MODULES
Module connectors are a proposed contract, NOT raw sensor IC pinouts. Pull-ups/decoupling and module supply requirements remain TBD.
4. FOUR BRUSHED MOTOR CHANNELS / LOW-SIDE SWITCHES
M0_RL_CCW
M1_RR_CW
M2_FR_CCW
M3_FL_CW
5. BATTERY ADC / DEFAULT OPEN LINK
JP1 stays OPEN until ADC power-off injection is checked. Q1-Q4: pin 1=G, 2=S, 3=D (different from old GDS tutorial). D1-D4: pin 1=K to V_bat; pin 2=A to motor negative. No selected MOSFET/diode/regulator part numbers. Board: 60 x 60 mm placement study, 2 layers, UNROUTED.

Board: 2 copper layers, 33 parts (0 on the bottom side), 24 nets, no tracks yet.
